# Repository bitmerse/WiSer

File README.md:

# WiSer

Experience seamless wireless serial connectivity with **WiSer**, a powerful set of two devices (**WiSer-USB** and **WiSer-TTL**) designed to facilitate a serial connection between your PC and embedded devices. Say goodbye to cumbersome USB cables and enjoy the freedom of wireless serial communication.

### Connection Diagram

WiSer is a fully **Open Source** project. All hardware design files, firmware source code, and documentation are made available so you can inspect its inner workings. Our goal is to empower users, making it easy to program, understand, customize, and troubleshoot WiSer.

# :file_folder: Repository contents
  - **/docs** - Documentation resources (Licensed under [CC BY-SA 4.0](docs/LICENSE))
  - **/hw** - Board design files (Licensed under [CERN-OHL-P-2.0](hw/LICENSE))
  - **/src** - Firmware source code (Licensed under [MIT](src/LICENSE))

# :blue_book: Documentation
  - [WiSer Product Page](https://bitmerse.com/products/wiser/)
  - [WiSer Quick Start Guide](https://bitmerse.gitbook.io/wiser-quick-start-guide/)
  - [WiSer Product Manual](https://bitmerse.gitbook.io/wiser-product-manual/)
  - [WiSer Specification](https://bitmerse.gitbook.io/wiser-product-spec-sheet/)

# :shopping_cart: Purchase Options
WiSer is currently available for purchase through the following platform:
 - [Crowd Supply](https://www.crowdsupply.com/bitmerse/wiser)

# :left_speech_bubble: Need Customization?
Do you need assistance customizing WiSer hardware or firmware to integrate into your product? Feel free to reach out to us via email below to explore and take advantage of our commercial services.
- e-mail: [contact@bitmerse.com](mailto:contact@bitmerse.com)
- website: [bitmerse.com](https://www.bitmerse.com)

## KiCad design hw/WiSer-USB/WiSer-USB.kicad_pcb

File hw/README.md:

# WiSer Hardware

This directory contains the hardware design files for WiSer-USB and WiSer-TTL, created using KiCad EDA.

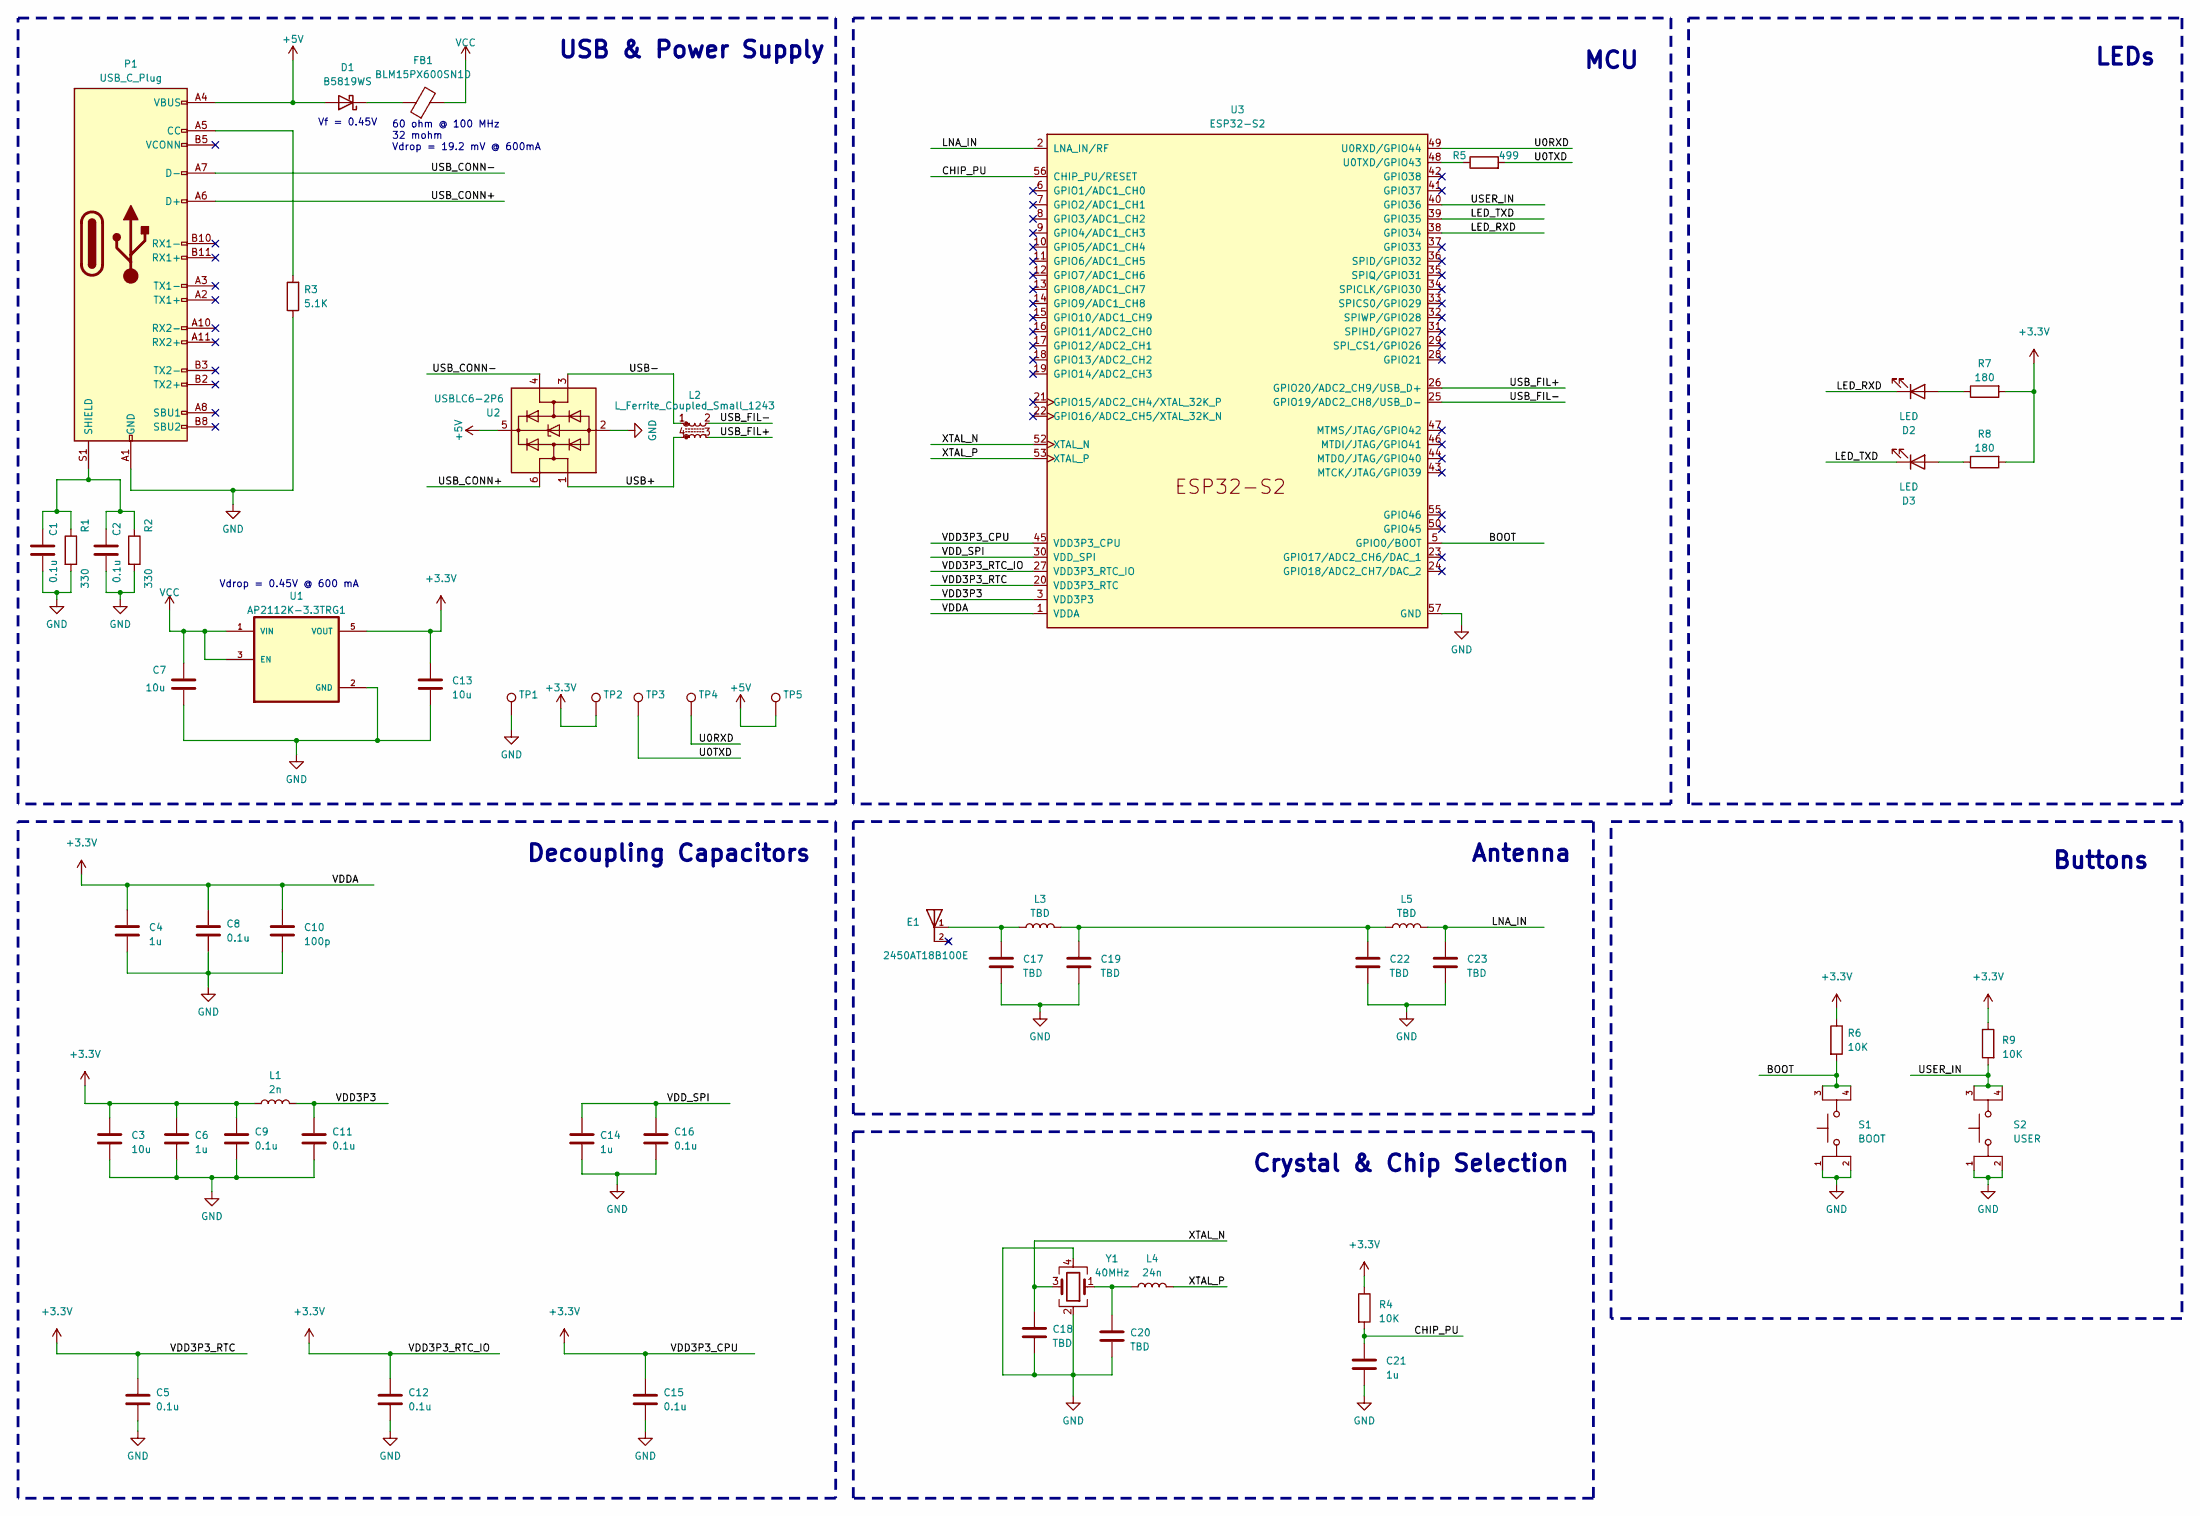
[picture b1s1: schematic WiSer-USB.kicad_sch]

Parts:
C1, C2, C5, C8, C9, C11, C12, C15, C16: 0.1u; C_0402_1005Metric
C3, C7, C13: 10u; C_0402_1005Metric
C4, C6, C14, C21: 1u; C_0402_1005Metric
C10: 100p; C_0402_1005Metric
C17, C18, C19, C20, C22, C23: TBD; C_0402_1005Metric
D1: B5819WS; D_SOD-323_HandSoldering
D2, D3: LED; LED_0402_1005Metric_Pad0.77x0.64mm_HandSolder
E1: 2450AT18B100E; XDCR_2450AT18B100E; PARTREV 4.0
FB1: BLM15PX600SN1D; R_0402_1005Metric
L1: 2n; L_0402_1005Metric
L2: L_Ferrite_Coupled_Small_1243; FIL_DLM0NSM900HY2D
L3, L5: TBD; L_0402_1005Metric
L4: 24n; L_0402_1005Metric
P1: USB_C_Plug; USB-C-Male-Conn
R1, R2: 330; R_0402_1005Metric
R3: 5.1K; R_0402_1005Metric
R4, R6, R9: 10K; R_0402_1005Metric
R5: 499; R_0402_1005Metric
R7, R8: 180; R_0402_1005Metric
S1: BOOT; SW_TL3365AF180QG; PARTREV A
S2: USER; SW_TL3365AF180QG; PARTREV A
TP1: GND; TestPoint_Pad_D0.8mm
TP2: 3V3; TestPoint_Pad_D0.8mm
TP3: U0RXD; TestPoint_Pad_D0.8mm
TP4: U0TXD; TestPoint_Pad_D0.8mm
TP5: 5V; TestPoint_Pad_D0.8mm
U1: AP2112K-3.3TRG1; SOT95P285X140-5N; PARTREV 2-2
U2: USBLC6-2P6; SOT50P160X60-6N
U3: ESP32-S2
Y1: 40MHz; Crystal_SMD_2016-4Pin_2.0x1.6mm

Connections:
+3V3: C3.1, C4.1, C5.1, C6.1, C8.1, C9.1, C10.1, C12.1, C13.1, C15.1, L1.1, R4.1, R6.1, R7.2, R8.2, R9.1, TP2.1, U1.5 (VOUT), U3.1 (VDDA), U3.20 (VDD3P3_RTC), U3.27 (VDD3P3_RTC_IO), U3.45 (VDD3P3_CPU), U3.51 (VDDA), U3.54 (VDDA)
+5V: D1.2 (A), P1.A4 (VBUS), P1.A9 (VBUS), P1.B4 (VBUS), P1.B9 (VBUS), TP5.1, U2.5 (VBUS)
/BOOT: R6.2, S1.3, S1.4, U3.5 (GPIO0/BOOT)
/CHIP_PU: C21.1, R4.2, U3.56 (CHIP_PU/RESET)
/LED_RXD: D2.1 (K), U3.38 (GPIO34)
/LED_TXD: D3.1 (K), U3.39 (GPIO35)
/LNA_IN: C23.1, L5.1, U3.2 (LNA_IN/RF)
/U0RXD: TP4.1, U3.49 (U0RXD/GPIO44)
/U0TXD: R5.2, TP3.1
/USB+: L2.4, U2.1 (I/O1)
/USB-: L2.1, U2.3 (I/O2)
/USB_CONN+: P1.A6 (D+), U2.6 (I/O1)
/USB_CONN-: P1.A7 (D-), U2.4 (I/O2)
/USB_FIL+: L2.3, U3.26 (GPIO20/ADC2_CH9/USB_D+)
/USB_FIL-: L2.2, U3.25 (GPIO19/ADC2_CH8/USB_D-)
/USER_IN: R9.2, S2.3, S2.4, U3.40 (GPIO36)
/VDD3P3: C11.1, L1.2, U3.3 (VDD3P3), U3.4 (VDD3P3)
/VDD_SPI: C14.1, C16.1, U3.30 (VDD_SPI)
/XTAL_N: C18.1, U3.52 (XTAL_N), Y1.3
/XTAL_P: L4.2, U3.53 (XTAL_P)
GND: C1.2, C2.2, C3.2, C4.2, C5.2, C6.2, C7.2, C8.2, C9.2, C10.2, C11.2, C12.2, C13.2, C14.2, C15.2, C16.2, C17.2, C18.2, C19.2, C20.2, C21.2, C22.2, C23.2, P1.A1 (GND), P1.A12 (GND), P1.B1 (GND), P1.B12 (GND), R1.2, R2.2, R3.1, S1.1, S1.2, S2.1, S2.2, TP1.1, U1.2 (GND), U2.2 (GND), U3.57 (GND), Y1.2, Y1.4
unnamed: C17.1, E1.1, L3.2
unnamed: C19.1, C22.1, L3.1, L5.2
unnamed: C20.1, L4.1, Y1.1
unnamed: D1.1 (K), FB1.1
unnamed: D2.2 (A), R7.1
unnamed: D3.2 (A), R8.1
unnamed: P1.A5 (CC), R3.2
unnamed: C1.1, C2.1, P1.S1 (SHIELD), R1.1, R2.1
unnamed: R5.1, U3.48 (U0TXD/GPIO43)
VCC: C7.1, FB1.2, U1.1 (VIN), U1.3 (EN)

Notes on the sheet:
Crystal & Chip Selection
Vf = 0.45V
LEDs
Decoupling Capacitors
Buttons
USB & Power Supply
60 ohm @ 100 MHz 32 mohm Vdrop = 19.2 mV @ 600mA
Antenna
MCU
Vdrop = 0.45V @ 600 mA

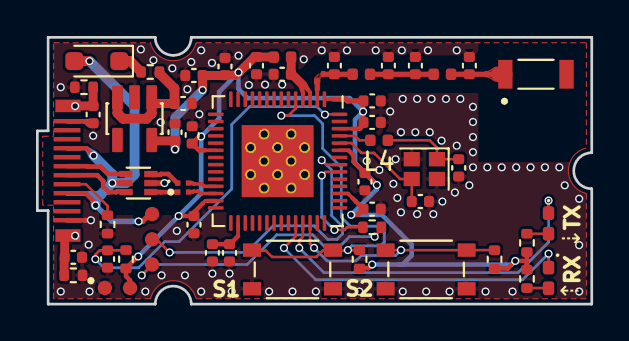
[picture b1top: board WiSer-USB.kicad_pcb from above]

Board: 4 copper layers, 30.8 x 14.8 mm, 54 parts (0 on the bottom side), 31 nets.

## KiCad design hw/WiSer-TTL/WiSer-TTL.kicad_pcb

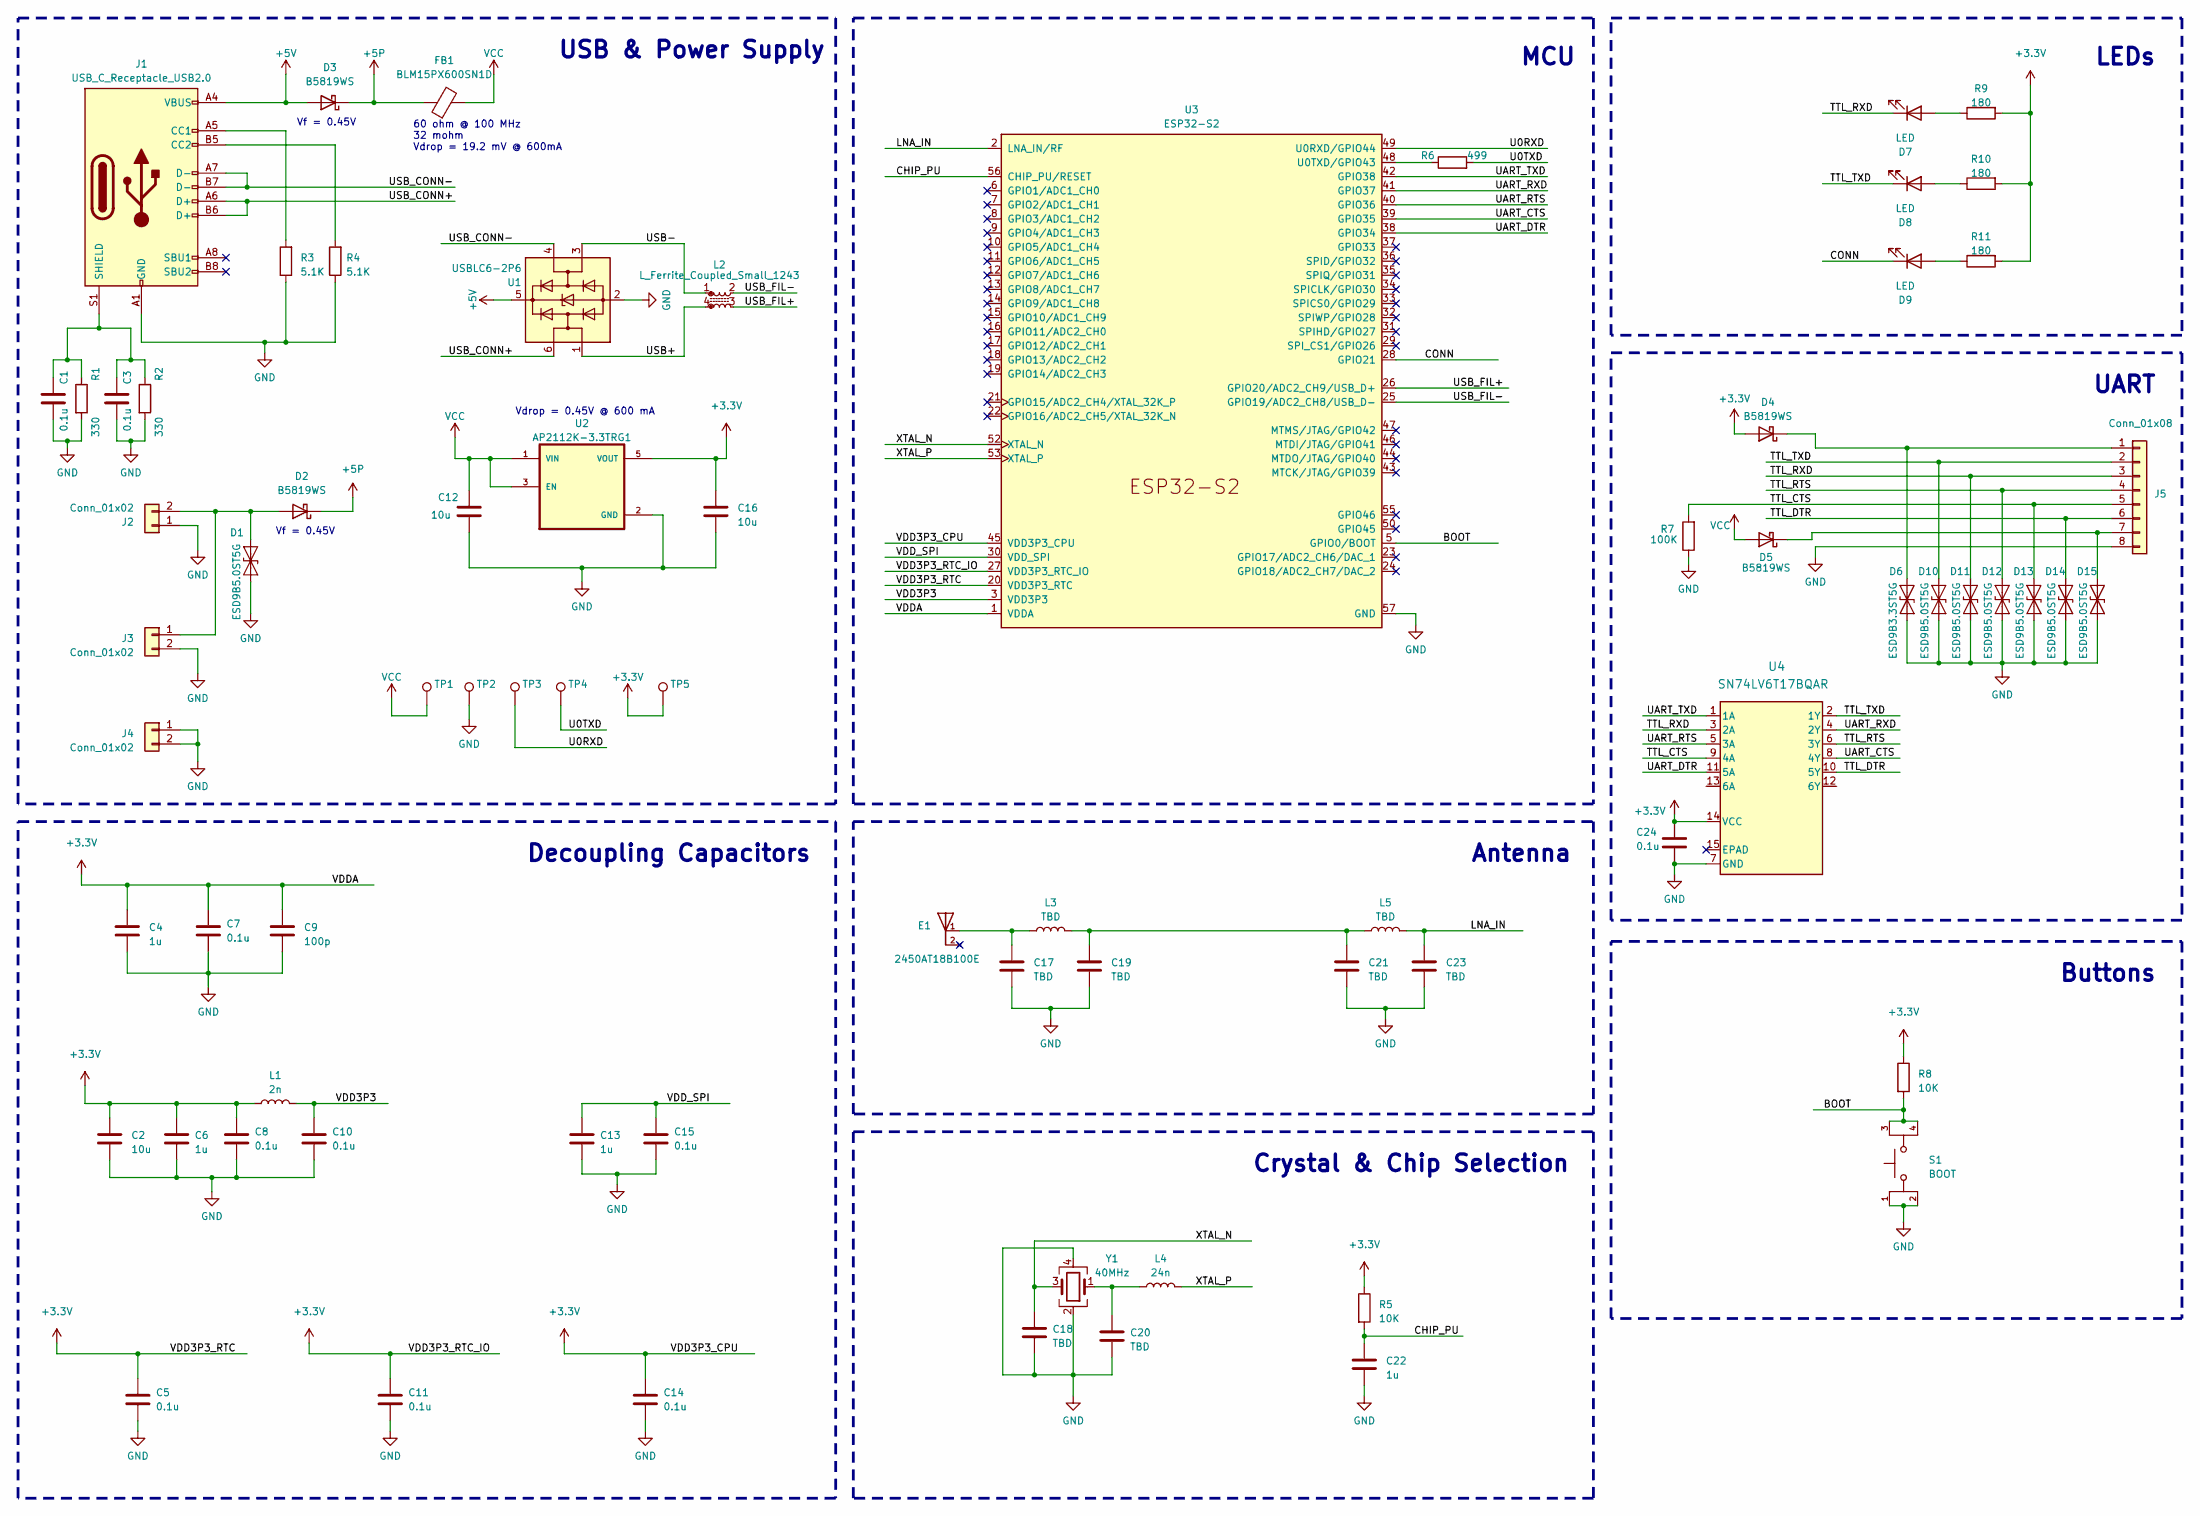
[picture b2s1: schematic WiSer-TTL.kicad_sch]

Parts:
C1, C3, C5, C7, C8, C10, C11, C14, C15, C24: 0.1u; C_0402_1005Metric
C2, C12, C16: 10u; C_0402_1005Metric
C4, C6, C13, C22: 1u; C_0402_1005Metric
C9: 100p; C_0402_1005Metric
C17, C18, C19, C20, C21, C23: TBD; C_0402_1005Metric
D1, D10, D11, D12, D13, D14, D15: ESD9B5.0ST5G; D_SOD-923
D2, D3, D4, D5: B5819WS; D_SOD-323_HandSoldering
D6: ESD9B3.3ST5G; D_SOD-923
D7, D8, D9: LED; LED_0402_1005Metric_Pad0.77x0.64mm_HandSolder
E1: 2450AT18B100E; XDCR_2450AT18B100E; PARTREV 4.0
FB1: BLM15PX600SN1D; R_0402_1005Metric
J1: USB_C_Receptacle_USB2.0; USB_C_Receptacle_G-Switch_GT-USB-7010ASV
J2: Conn_01x02; PinHeader_1x02_P2.54mm_Horizontal
J3, J4: Conn_01x02; PinHeader_1x02_P2.54mm_Vertical
J5: Conn_01x08; PinHeader_1x08_P2.54mm_Horizontal
L1: 2n; L_0402_1005Metric
L2: L_Ferrite_Coupled_Small_1243; FIL_DLM0NSM900HY2D
L3, L5: TBD; L_0402_1005Metric
L4: 24n; L_0402_1005Metric
R1, R2: 330; R_0402_1005Metric
R3, R4: 5.1K; R_0402_1005Metric
R5, R8: 10K; R_0402_1005Metric
R6: 499; R_0402_1005Metric
R7: 100K; R_0402_1005Metric
R9, R10, R11: 180; R_0402_1005Metric
S1: BOOT; SW_TL3365AF180QG; PARTREV A
TP1: 5V; TestPoint_Pad_D0.8mm
TP2, TP4: GND; TestPoint_Pad_D0.8mm
TP3: U0RXD; TestPoint_Pad_D0.8mm
TP5: 3V3; TestPoint_Pad_D0.8mm
U1: USBLC6-2P6; SOT50P160X60-6N
U2: AP2112K-3.3TRG1; SOT95P285X140-5N; PARTREV 2-2
U3: ESP32-S2
U4: SN74LV6T17BQAR; WQFN14_BQA_TEX
Y1: 40MHz; Crystal_SMD_2016-4Pin_2.0x1.6mm

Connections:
+3V3: C2.1, C4.1, C5.1, C6.1, C7.1, C8.1, C9.1, C11.1, C14.1, C16.1, C24.1, D4.2 (A), L1.1, R5.1, R8.1, R9.2, R10.2, R11.2, TP5.1, U2.5 (VOUT), U3.1 (VDDA), U3.20 (VDD3P3_RTC), U3.27 (VDD3P3_RTC_IO), U3.45 (VDD3P3_CPU), U3.51 (VDDA), U3.54 (VDDA), U4.14 (VCC)
+5P: D2.1 (K), D3.1 (K), FB1.1
+5V: D3.2 (A), J1.A4 (VBUS), J1.A9 (VBUS), J1.B4 (VBUS), J1.B9 (VBUS), U1.5 (VBUS)
/BOOT: R8.2, S1.3, S1.4, U3.5 (GPIO0/BOOT)
/CHIP_PU: C22.1, R5.2, U3.56 (CHIP_PU/RESET)
/CONN: D9.1 (K), U3.28 (GPIO21)
/LNA_IN: C23.1, L5.2, U3.2 (LNA_IN/RF)
/TTL_CTS: D13.2 (A2), J5.5, R7.2, U4.9 (4A)
/TTL_DTR: D14.2 (A2), J5.6, U4.10 (5Y)
/TTL_RTS: D12.2 (A2), J5.4, U4.6 (3Y)
/TTL_RXD: D7.1 (K), D11.2 (A2), J5.3, U4.3 (2A)
/TTL_TXD: D8.1 (K), D10.2 (A2), J5.2, U4.2 (1Y)
/U0RXD: TP3.1, U3.49 (U0RXD/GPIO44)
/U0TXD: R6.2, TP4.1
/UART_CTS: U3.39 (GPIO35), U4.8 (4Y)
/UART_DTR: U3.38 (GPIO34), U4.11 (5A)
/UART_RTS: U3.40 (GPIO36), U4.5 (3A)
/UART_RXD: U3.41 (GPIO37), U4.4 (2Y)
/UART_TXD: U3.42 (GPIO38), U4.1 (1A)
/USB+: L2.4, U1.1 (I/O1)
/USB-: L2.1, U1.3 (I/O2)
/USB_CONN+: J1.A6 (D+), J1.B6 (D+), U1.6 (I/O1)
/USB_CONN-: J1.A7 (D-), J1.B7 (D-), U1.4 (I/O2)
/USB_FIL+: L2.3, U3.26 (GPIO20/ADC2_CH9/USB_D+)
/USB_FIL-: L2.2, U3.25 (GPIO19/ADC2_CH8/USB_D-)
/VDD3P3: C10.1, L1.2, U3.3 (VDD3P3), U3.4 (VDD3P3)
/VDD_SPI: C13.1, C15.1, U3.30 (VDD_SPI)
/XTAL_N: C18.1, U3.52 (XTAL_N), Y1.3
/XTAL_P: L4.2, U3.53 (XTAL_P)
GND: C1.2, C2.2, C3.2, C4.2, C5.2, C6.2, C7.2, C8.2, C9.2, C10.2, C11.2, C12.2, C13.2, C14.2, C15.2, C16.2, C17.2, C18.2, C19.2, C20.2, C21.2, C22.2, C23.2, C24.2, D1.1 (A1), D6.1 (A1), D10.1 (A1), D11.1 (A1), D12.1 (A1), D13.1 (A1), D14.1 (A1), D15.1 (A1), J1.A1 (GND), J1.A12 (GND), J1.B1 (GND), J1.B12 (GND), J2.1, J3.2, J4.1, J4.2, J5.8, R1.2, R2.2, R3.1, R4.1, R7.1, S1.1, S1.2, TP2.1, U1.2 (GND), U2.2 (GND), U3.57 (GND), U4.7 (GND), Y1.2, Y1.4
unnamed: C17.1, E1.1, L3.1
unnamed: C19.1, C21.1, L3.2, L5.1
unnamed: C20.1, L4.1, Y1.1
unnamed: D1.2 (A2), D2.2 (A), J2.2, J3.1
unnamed: D4.1 (K), D6.2 (A2), J5.1
unnamed: D7.2 (A), R9.1
unnamed: D8.2 (A), R10.1
unnamed: D9.2 (A), R11.1
unnamed: D5.1 (K), D15.2 (A2), J5.7
unnamed: J1.A5 (CC1), R3.2
unnamed: J1.B5 (CC2), R4.2
unnamed: C1.1, C3.1, J1.S1 (SHIELD), R1.1, R2.1
unnamed: R6.1, U3.48 (U0TXD/GPIO43)
VCC: C12.1, D5.2 (A), FB1.2, TP1.1, U2.1 (VIN), U2.3 (EN)

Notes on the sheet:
Crystal & Chip Selection
LEDs
Decoupling Capacitors
Vf = 0.45V
Buttons
USB & Power Supply
UART
Antenna
MCU
60 ohm @ 100 MHz 32 mohm Vdrop = 19.2 mV @ 600mA
Vdrop = 0.45V @ 600 mA

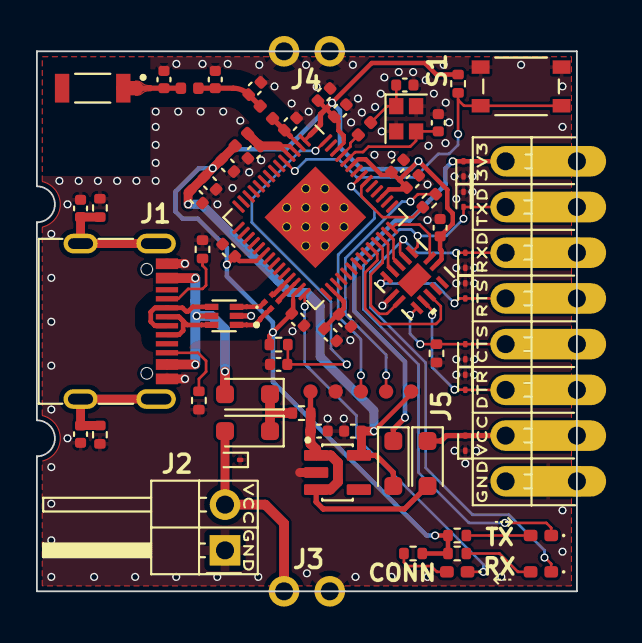
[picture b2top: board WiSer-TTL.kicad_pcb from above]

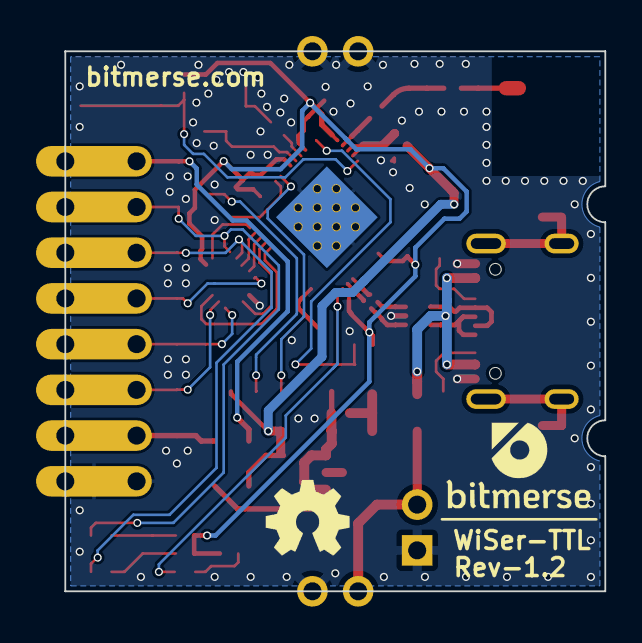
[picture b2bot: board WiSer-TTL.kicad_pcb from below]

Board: 4 copper layers, 30.0 x 30.0 mm, 75 parts (2 on the bottom side), 44 nets.

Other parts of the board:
G1, G2: LOGO

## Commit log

2023-09-07 Add directories for holding firmware, hardware & docs
2023-09-07 Add readme
2023-12-09 GITBOOK-8: No subject
2023-12-09 GITBOOK-6: No subject
2023-12-09 GITBOOK-1: No subject
2023-12-13 GITBOOK-7: No subject
2023-12-14 GitBook: No commit message
2023-12-14 GITBOOK-9: No subject
2024-01-23 GITBOOK-10: No subject
2024-01-23 GITBOOK-11: No subject
2024-01-30 add firmware source code files
2024-01-30 add hardware design files
2024-02-02 add connection description
2024-02-19 add broadcast mode feature in firmware
2024-02-20 GITBOOK-13: No subject
2024-02-20 add note for default configuration in README file
2024-05-22 Update hardware design files

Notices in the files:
hw/WiSer-TTL/WiSer-TTL.kicad_pcb:
Copyright (c) 2024 Bitmerse LLP
This file is licensed under CERN-OHL-P-2.0
